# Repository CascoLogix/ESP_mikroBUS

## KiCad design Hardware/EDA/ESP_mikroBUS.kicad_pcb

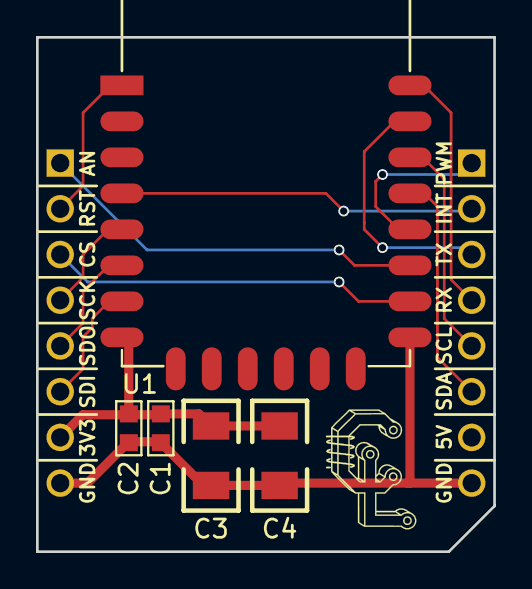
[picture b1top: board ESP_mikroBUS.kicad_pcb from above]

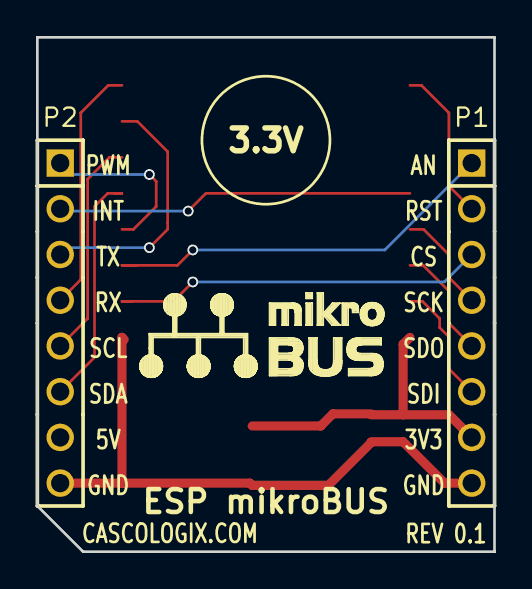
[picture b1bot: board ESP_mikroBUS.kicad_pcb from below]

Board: 2 copper layers, 25.4 x 28.6 mm, 7 parts (2 on the bottom side), 14 nets.

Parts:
C1: 0.1uF; C0603
C2: 1uF; C0603
C3, C4: 47uF; 1206
P1, P2: HEADER_M_2.54MM_1R8P_ST_AU_PTH
U1: ESP-12E

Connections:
+3.3V: C1.1, C2.1, C3.1, C4.1, P1.7, U1.8
AN: P1.1, U1.17
CS: P1.3, U1.16
GND: C1.2, C2.2, C3.2, C4.2, P1.8, P2.8, U1.15
INT: P2.2, U1.4
MISO: P1.5, U1.6
MOSI: P1.6, U1.7
PWM: P2.1, U1.18
RST: P1.2, U1.1
RX: P2.3, U1.21
SCK: P1.4, U1.5
SCL: P2.5, U1.20
SDA: P2.6, U1.19
TX: P2.4, U1.22

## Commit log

2016-11-29 First commit. Rev 0.1 ordered from OSH Park.
